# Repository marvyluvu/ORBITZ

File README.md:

<h1 align="center">ORBITZ</h1>

<p align="center">
  <i>Desktop satellite, plane, and ISS tracker with a Console-style display and LED halo.</i>
</p>

---

##  1. What is ORBITZ

<p>
Orbit is a desktop satellite, plane, and ISS tracker with a radar-style display, LED halo, live ADS-B plane data, and GPS aware tracking
</p>

---

##  2. Why did I make it?

<p>
I personally love astronomy and being able to stargaze outside with the stars, but I could never catch a satellite or the ISS due to how fast they orbit, so when I heard of FALLOUT by hackclub, I saw this as the perfect opportunity to work and bring my idea to life!!
</p>

---

##  3. How does it work?

The brains of the operation is a Raspberry Pi Zero 2W. It:
-  Fetches TLEs from CelesTrak and uses Skyfield to compute live satellite and ISS passes.
-  Reads your location from GPSD (USB GPS) or falls back to a configured location.\
-  Receives live ADS‑B aircraft data either from a local RTL‑SDR + dump1090 or from the OpenSky API.
-  The display shows a radar view, the LED halo indicates visibility, and the buzzer alerts you before passes so you don’t miss them.

---

##  4.Hardware schematic

<p>
You can view the full schematic for the ORBITZ PCB below.
  </p>

---

##  5. How do you use it?

<p>
Plug it into usb c, Connect it to wifi, and it shows satellites and planes passing over your location
using the rotary dial and the button, you can scroll through targets and select them
</p>

If you plug in the USB GPS AND SDR DONGLE, Orbitz will automagically :
-  use gpsd for your location
-  use live ADS-B data from planes flying nearby for fully local tracking (or fall back to Opensky if no receiver is present)
---

## 6. Assembly:

1. First print the enclosure, and order all the items in the BOM.
2. Insert heat inserts in all screw standoffs.
3. insert battery into pcb.
4. insert pcb into enclosure, and make sure the battery is UNDER the pcb.
5. screw in pcb board.
6. attach screen with screws (MAKE SURE ITS ORIENTED PROPERLY with the row of pins pointing upwards)
7. insert joystick and wire to the pcb
8. cut rgb strip to size, then stick near the top of the enclosure.
9. wire rgb strip to pcb board.
10. Attach acrylic lid and back.
11. using super glue, attach the usb hub to the slot.
12. connect both the GPS and SDR dongle to the usb hub.
13. connect to power, flash firmware and enjoy!

## ASSEMBLED DESIGN 
Below is what your fully assembled design should look like.

---

## 7. Firmware

There are two ways to run ORBITZ:

### 7.1 Desktop/mock firmware (no hardware required)

This runs the radar UI in a Pygame window on any PC or Pi, using mock drivers instead of the real display, LEDs, and buttons.

How to run (Windows / PowerShell):

1. Open a terminal in the `firmware` folder.
2. `python -m venv .venv`
3. `.\.venv\Scripts\Activate.ps1`
4. `pip install -r requirements.txt`
5. `python main.py`

Controls in mock mode:

- `m` + Enter: toggle between PLANES and SATS/ISS modes.
- `j` / `k` + Enter: move selection to next/previous target.
- `q` + Enter: quit.

### 7.2 Hardware firmware (Pi + PCB)

On the Pi Zero 2W with the ORBITZ PCB attached:

- The display shows the radar UI.
- The rotary encoder controls target selection.
- The encoder button toggles modes.
- The LED halo and buzzer reflect visibility/alerts.
- GPSD and dump1090/readsb are used automatically if available.

##  8. Images

<table>
  <tr>
    <td align="center">
      <strong>FINAL PCB SCREENSHOTS</strong><br><br>
      
    </td>
  </tr>
  <tr>
    <td align="center">
      <strong>PCB</strong><br><br>
      
    </td>
  </tr>
  <tr>
    <td align="center">
      <strong>FINAL BUILD</strong><br><br>
      
    </td>
  </tr>
</table>

##  9. Bill of Materials (BOM)

The full detailed BOM is included in this repository:

- [`/ORBITZ_BILL_OF_MATERIALS.csv`](https://github.com/marvyluvu/ORBITZ/blob/main/hardware/BOM.csv)

You can open this file in Excel, Google Sheets, or any spreadsheet tool.
It includes part names, descriptions, quantities, prices, and direct purchase links.

Key components

| Product name          | Description                                      | Qty |
|-----------------------|--------------------------------------------------|-----|
| Raspberry Pi Zero 2W  | Main computer, runs satellite tracking software  | 1   |
| 2.4" NO TOUCH ILI9341| SPI LCD display for Orbitz radar UI              | 1   |
| WS2812B LED STRIP     | Internal RGB status lighting (1 m)              | 1   |
| RTL‑SDR USB dongle    | ADS‑B receiver for local aircraft (dump1090)    | 1   |
| USB GPS dongle (VK‑172 or similar) | Provides live GPS position via GPSD | 1   |

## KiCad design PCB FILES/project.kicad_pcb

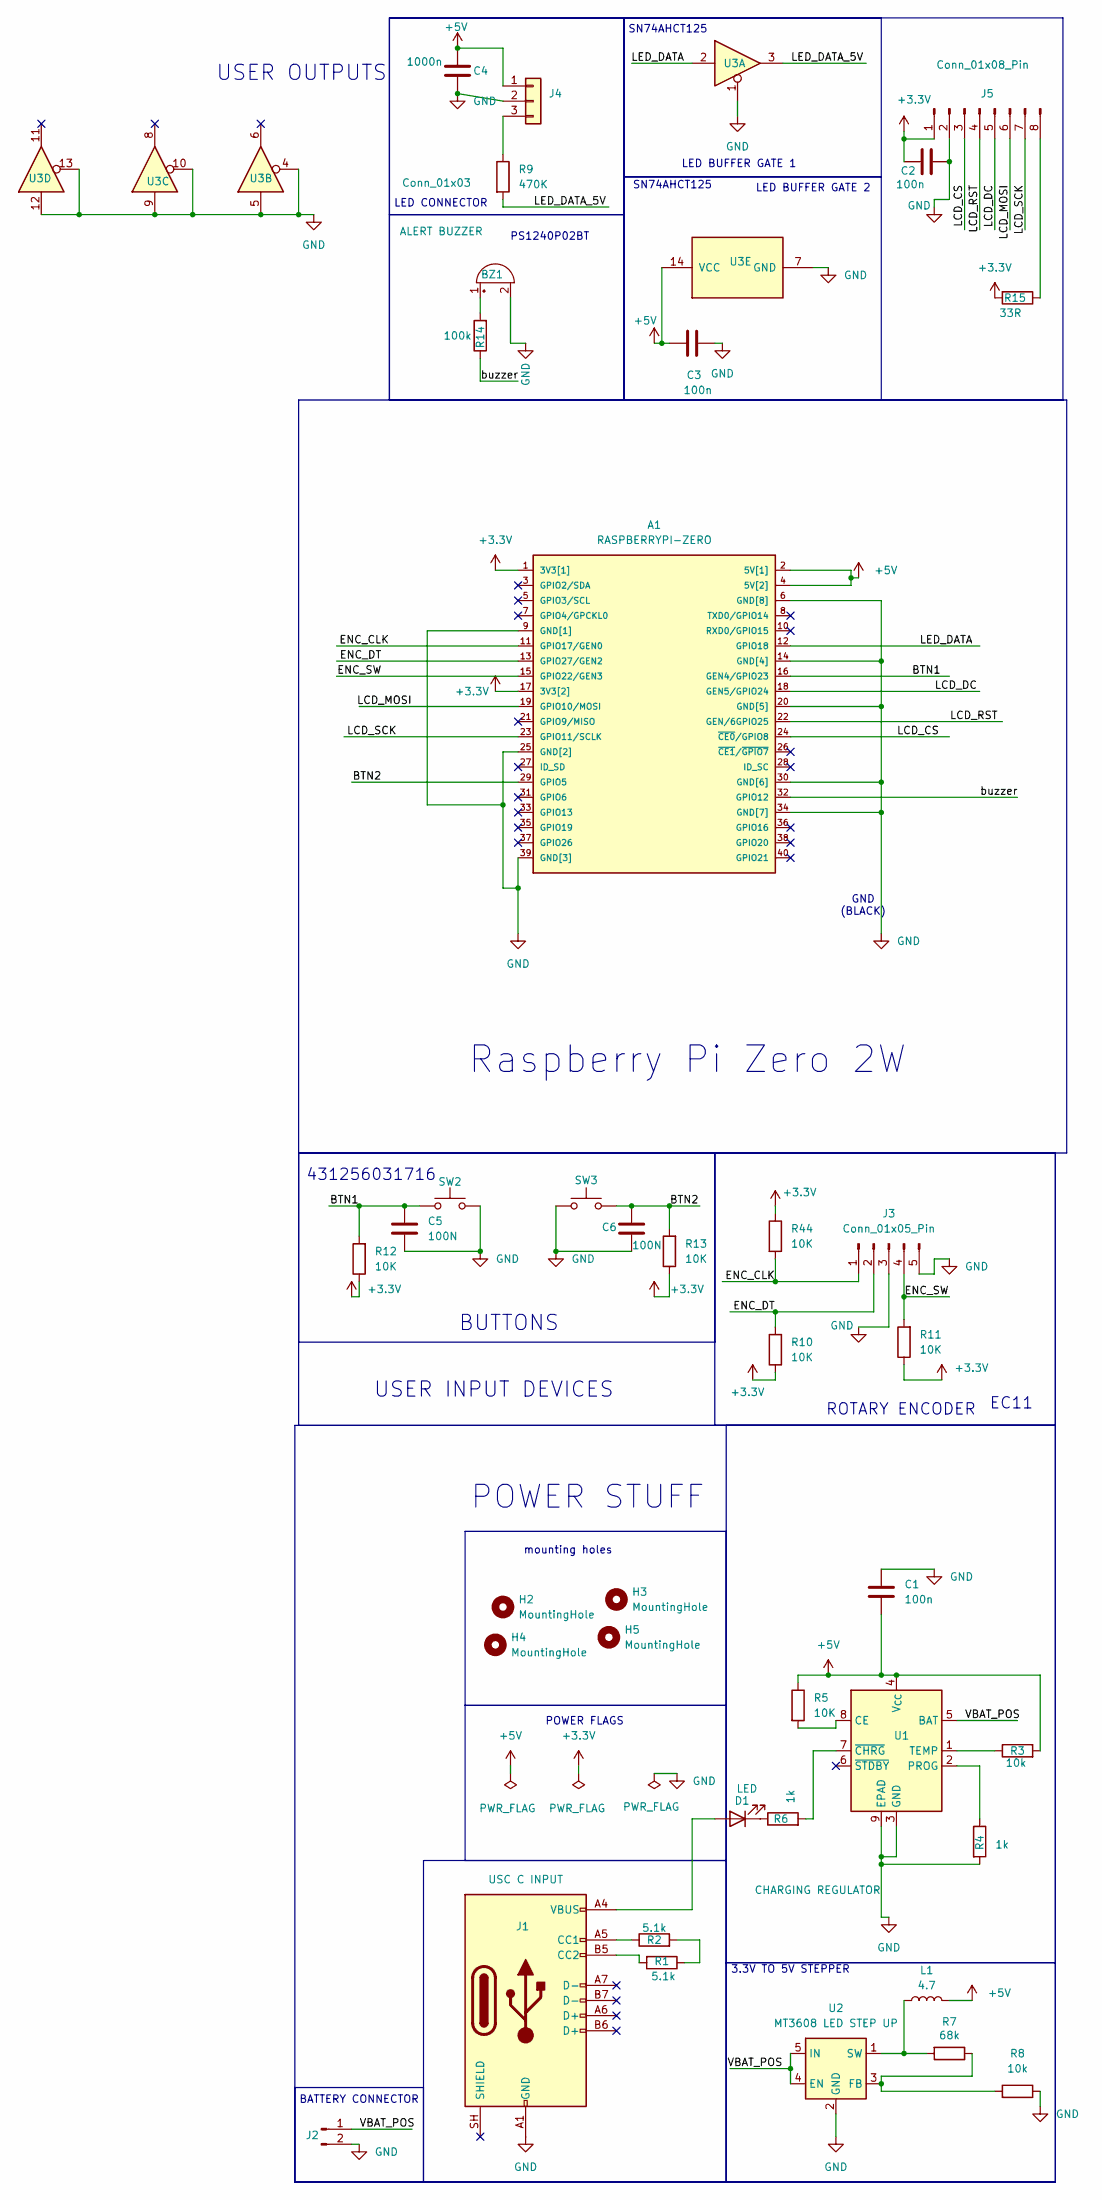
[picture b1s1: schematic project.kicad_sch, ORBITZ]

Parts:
A1: RASPBERRYPI-ZERO; RASPBERRYPI-ZERO_RPI-ZERO
BZ1: ALERT BUZZER; Buzzer_TDK_PS1240P02BT_D12.2mm_H6.5mm
C1, C2, C3: 100n; C_1206_3216Metric
C4: 1000n; CP_Radial_D8.0mm_P3.50mm
C5, C6: 100N; C_1206_3216Metric
D1: LED; LED_1206_3216Metric
H2, H3, H4, H5: MountingHole; MountingHole_3.2mm_M3
J1: USC C INPUT; USB_C_Receptacle_HRO_TYPE-C-31-M-12
J2: batt connector; JST_PH_S2B-PH-K_1x02_P2.00mm_Horizontal
J3: Conn_01x05_Pin; PinHeader_1x05_P2.54mm_Vertical
J4: Conn_01x03; PinHeader_1x03_P2.54mm_Vertical
J5: Conn_01x08_Pin; PinHeader_1x08_P2.54mm_Vertical
L1: 4.7; L_0805_2012Metric
R1, R2: 5.1k; R_1206_3216Metric
R3, R8: 10k; R_1206_3216Metric
R4, R6: 1k; R_1206_3216Metric
R5, R10, R11, R12, R13, R44: 10K; R_1206_3216Metric
R7: 68k; R_1206_3216Metric
R9: 470K; R_1206_3216Metric
R14: 100k; R_1206_3216Metric
R15: 33R; R_1206_3216Metric
SW2: selection button; SW_Tactile_SPST_Angled_PTS645Vx31-2LFS
SW3: selection button 2; SW_Tactile_SPST_Angled_PTS645Vx31-2LFS
U1: CHARGING REGULATOR; SOIC-8-1EP_3.9x4.9mm_P1.27mm_EP2.41x3.3mm_ThermalVias
U2: MT3608 LED STEP UP; SOT-23-6
U3: 74AHCT125; SOIC-14_3.9x8.7mm_P1.27mm

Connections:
+3.3V: A1.1 (3V3[1]), A1.17 (3V3[2]), C2.1, J5.1, R10.1, R11.1, R12.1, R13.1, R15.2, R44.1
+5V: A1.2 (5V[1]), A1.4 (5V[2]), C1.2, C3.1, C4.1, J4.1, L1.2, R3.2, R5.1, U1.4 (V_{CC}), U3.14 (VCC)
/BTN1: A1.16 (GEN4/GPIO23), C5.1, R12.2, SW2.1
/BTN2: A1.29 (GPIO5), C6.1, R13.2, SW3.2
/ENC_CLK: A1.11 (GPIO17/GEN0), J3.1, R44.2
/ENC_DT: A1.13 (GPIO27/GEN2), J3.2, R10.2
/ENC_SW: A1.15 (GPIO22/GEN3), J3.4, R11.2
/LCD_CS: A1.24 (~CE0/GPIO8), J5.3
/LCD_DC: A1.18 (GEN5/GPIO24), J5.5
/LCD_MOSI: A1.19 (GPIO10/MOSI), J5.6
/LCD_RST: A1.22 (GEN/6GPIO25), J5.4
/LCD_SCK: A1.23 (GPIO11/SCLK), J5.7
/LED_DATA: A1.12 (GPIO18), U3.2
/LED_DATA_5V: R9.2, U3.3
/VBAT_POS: J2.1, U1.5 (BAT), U2.4 (EN), U2.5 (IN)
/buzzer: A1.32 (GPIO12), R14.1
GND: A1.6 (GND[8]), A1.9 (GND[1]), A1.14 (GND[4]), A1.20 (GND[5]), A1.25 (GND[2]), A1.30 (GND[6]), A1.34 (GND[7]), A1.39 (GND[3]), BZ1.2 (-), C1.1, C2.2, C3.2, C4.2, C5.2, C6.2, J1.A1 (GND), J1.A12 (GND), J1.B1 (GND), J1.B12 (GND), J2.2, J3.3, J3.5, J4.2, J5.2, R4.2, R8.1, SW2.2, SW3.1, U1.3 (GND), U1.9 (EPAD), U2.2 (GND), U3.1, U3.4, U3.5, U3.7 (GND), U3.9, U3.10, U3.12, U3.13
unnamed: BZ1.1 (+), R14.2
unnamed: D1.2 (A), J1.A4 (VBUS), J1.A9 (VBUS), J1.B4 (VBUS), J1.B9 (VBUS)
unnamed: D1.1 (K), R6.1
unnamed: J1.A5 (CC1), R2.1
unnamed: J1.B5 (CC2), R1.2
unnamed: J4.3, R9.1
unnamed: J5.8, R15.1
unnamed: R1.1, R2.2
unnamed: R5.2, U1.8 (CE)
unnamed: R4.1, U1.2 (PROG)
unnamed: R3.1, U1.1 (TEMP)
unnamed: R6.2, U1.7 (~CHRG)
unnamed: R7.1, R8.2, U2.3 (FB)
unnamed: L1.1, R7.2, U2.1 (SW)

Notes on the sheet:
LED BUFFER GATE 1
USER INPUT DEVICES
SN74AHCT125
LED CONNECTOR
POWER FLAGS
3.3V TO 5V STEPPER
EC11
GND (BLACK)
431256031716
POWER STUFF
BUTTONS
PS1240P02BT
Raspberry Pi Zero 2W
ROTARY ENCODER
mounting holes
USER OUTPUTS
BATTERY CONNECTOR
LED BUFFER GATE 2

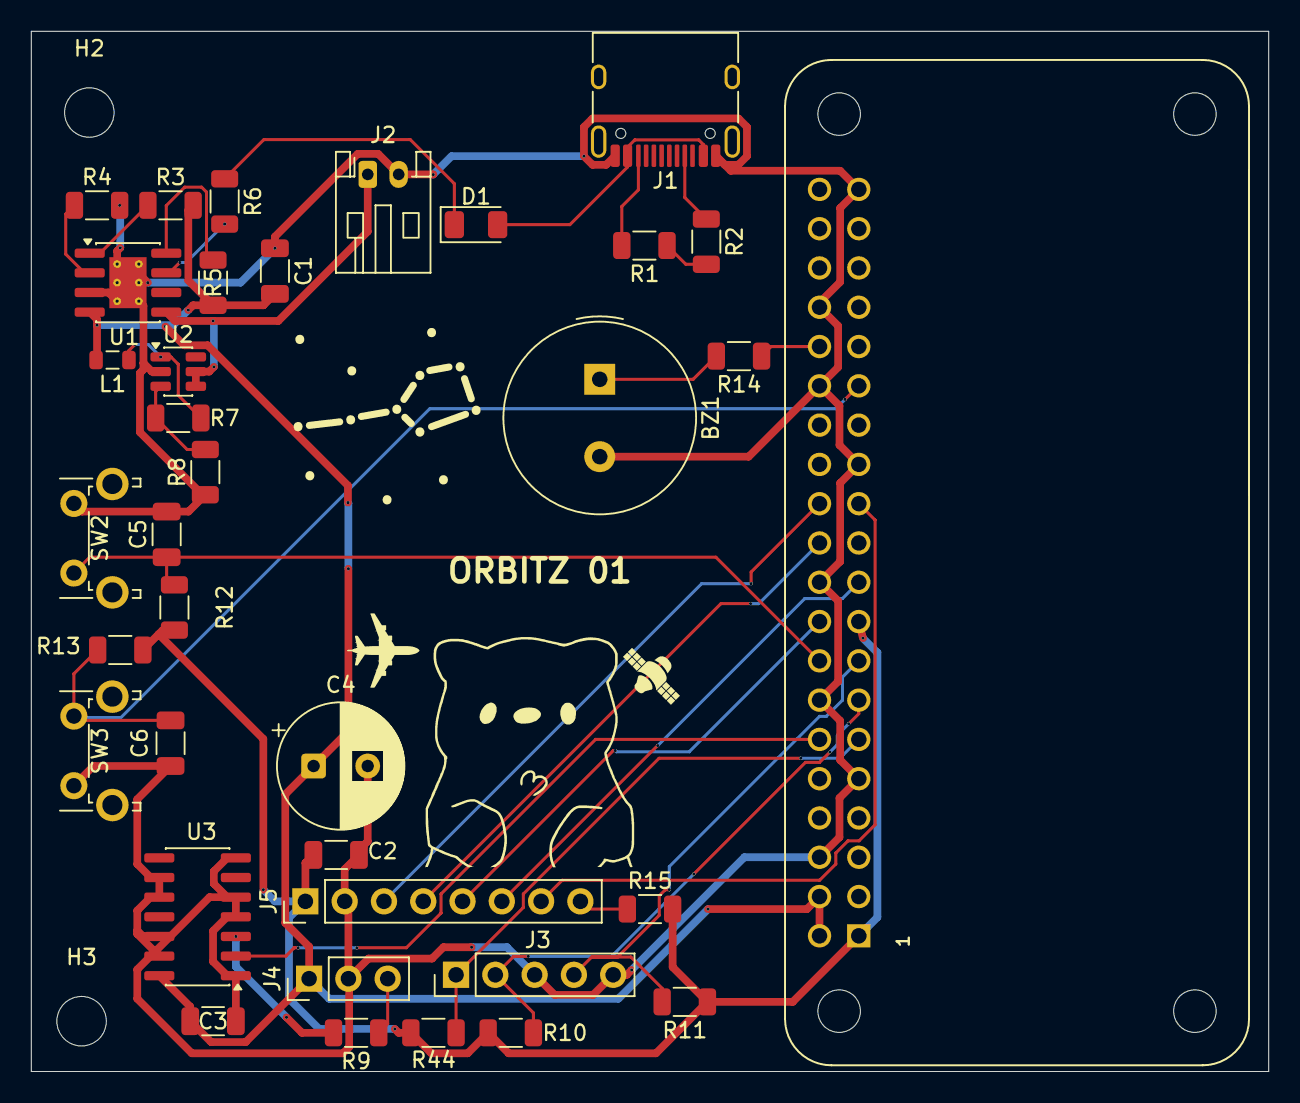
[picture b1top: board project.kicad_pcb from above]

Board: 2 copper layers, 80.0 x 67.2 mm, 38 parts (0 on the bottom side), 31 nets.

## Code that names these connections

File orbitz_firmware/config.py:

#SCREEN PINS

LCD_MOSI = 10
LCD_SCK = 11
LCD_CS = 8
LCD_DC = 24
LCD_RST = 25
LCD_WIDTH = 240
LCD_HEIGHT = 320
LCD_SPI_BUS = 0
LCD_SPI_DEVICE = 0

#ROTARY ENCODER

ENC_CLK = 17
ENC_DT = 27
ENC_SW = 22


#BUTTONS
BTN1 = 23
BTN2 = 5

#ALERTING

LED_DATA = 18
LED_COUNT = 8 #CHANGE IT TO YOUR ACTUAL LED COUNT 
BUZZER_PINS = 12

# Update these if you move the device

OBSERVER_LAT = 25.3463
OBSERVER_LON = 55.4209
OBSERVER_ELEV= 0

# OpenSky planes API
PLANES_API_URL = "https://opensky-network.org/api/states/all" 
PLANES_API_TIMEOUT = 1.5
PLANES_BBOX_DEGREES = 1.0 
PLANES_MAX_RANGE_KM = 400.0

# Local dump1090 /ADS-B
PLANES_LOCAL_URL = "http://pi/dump1090/data/aircraft.json" #PLACEHOLDER!!!!

PLANES_LOCAL_TIMEOUT = 0.3  

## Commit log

2026-04-12 Create HARDWARE
2026-04-29 Rename ORBITZ_GERBERS NEW.zip to ORBITZ_GERBERS.zip
2026-06-07 Rename ORBITZ - BOM (1).csv to ORBITZ - BILL OF MATERIALS.csv
2026-06-07 Create PCB FILES
2026-06-07 Create test
2026-06-12 Create T
2026-06-14 Create a
2026-06-14 Rename ORBITZ.pdf to zine/ORBITZ.pdf
2026-06-14 Rename ORBITZ (1).pdf to ORBITZ.pdf
2026-06-14 Rename ORBITZ - BOM (2).csv to BOM/ORBITZ - BILL OF MATERIALS.csv
2026-06-14 Rename ORBITZ .pdf to ZINE/ ORBITZ .pdf
2026-06-14 docs: rewrite README in clean Markdown
2026-06-14 revert: restore original README
2026-06-18 Rename orbitz.svg to orbitz_schematic.svg
2026-06-18 Rename ASSEMBLY.png to orbitz_case_interior.png
2026-06-20 Rename ORBITZ-BOM.csv to BOM.csv
2026-06-20 Fix formatting issue in assembly instructions
2026-06-24 step model
